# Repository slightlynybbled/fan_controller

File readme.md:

# Purpose #

This repository is for the hardware and firmware for a PC fan controller.  The
controller is intended to allow the user to multi-plex a single motherboard
output so that it may control up to 4 additional fans.  The project will feature:

 * Up to 4 outputs
 * Motherboard-controlled outputs for each with user speed scaling
 * Soft-start to reduce load on the motherboard
 * Speed control for each fan when a motherboard speed signal is not present
 
Details of the project may be found at [for(embed)](http://www.forembed.com/category/fan-controller.html).
 
# Project Status #

Firmware for v1.2 (optional thermistor control) is under development.

Firmware for v1.1 is complete!  Testing has been completely successful!

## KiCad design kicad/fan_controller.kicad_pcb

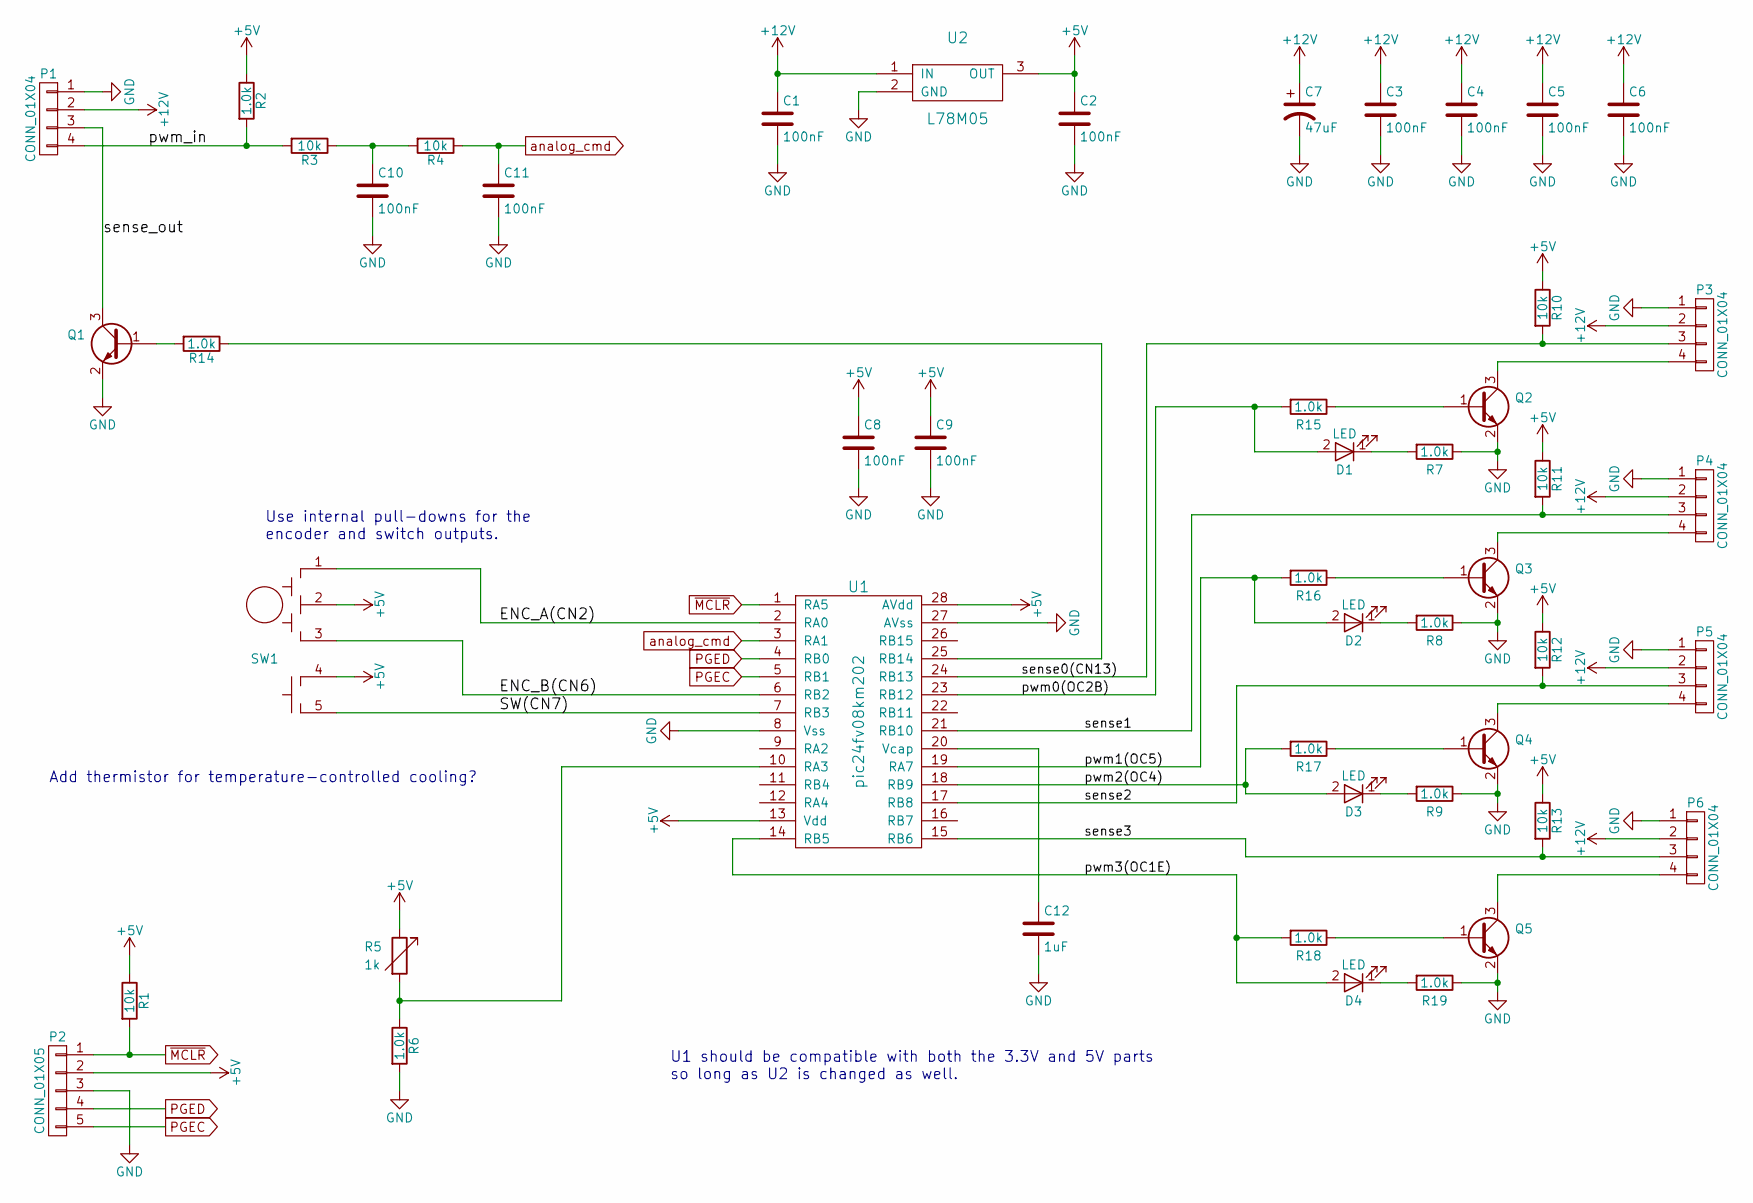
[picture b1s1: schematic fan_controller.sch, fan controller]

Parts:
C1, C2, C3, C4, C5, C6, C8, C9, C10, C11: 100nF; SM_0603; MPN CC0603ZRY5V7BB104
C7: 47uF; C_Radial_D5_L11_P2; MPN ESK476M035AC3AA
C12: 1uF; SM_0603; MPN CC0603ZRY5V7BB105
D1, D2, D3, D4: LED; D_0805; MPN LG R971-KN-1
P1, P3, P4, P5, P6: CONN_01X04; CONN_1x4_PC_FAN; MPN 47053-1000
P2: CONN_01X05; CON_1x5_0.1in
Q1, Q2, Q3, Q4, Q5: Q_NPN_BEC; SOT-23; MPN MMBT3904LT1G
R1, R3, R4, R10, R11, R12, R13: 10k; R_0603; MPN RC0603JR-0710KL
R2, R6, R7, R8, R9, R14, R15, R16, R17, R18, R19: 1.0k; R_0603; MPN RC0603JR-071KL
R5: 1k; D_0805; MPN NCP18XQ102J03RB
SW1: encoder_rotary_with_switch; encoder_EN12-HS; MPN EN12-HS22AF30
U1: pic24fv08km202; SSOP-28; MPN PIC24FV16KM202-I/SS
U2: L78M05; DPAK_TO-252; MPN MC7805CDTG

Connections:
+5V: C2.1, C8.1, C9.1, P2.2, R1.1, R2.1, R5.1, R10.1, R11.1, R12.1, R13.1, SW1.2, SW1.4, U1.13 (Vdd), U1.28 (AVdd), U2.3 (OUT)
+12V: C1.1, C3.1, C4.1, C5.1, C6.1, C7.1, P1.2, P3.2, P4.2, P5.2, P6.2, U2.1 (IN)
/ENC_A(CN2): SW1.1, U1.2 (RA0)
/ENC_B(CN6): SW1.3, U1.6 (RB2)
/SW(CN7): SW1.5, U1.7 (RB3)
/pwm0(OC2B): D1.2 (A), R15.2, U1.23 (RB12)
/pwm1(OC5): D2.2 (A), R16.2, U1.19 (RA7)
/pwm2(OC4): D3.2 (A), R17.2, U1.18 (RB9)
/pwm3(OC1E): D4.2 (A), R18.2, U1.14 (RB5)
/pwm_in: P1.4, R2.2, R3.2
/sense0(CN13): P3.3, R10.2, U1.24 (RB13)
/sense1: P4.3, R11.2, U1.21 (RB10)
/sense2: P5.3, R12.2, U1.17 (RB8)
/sense3: P6.3, R13.2, U1.15 (RB6)
/sense_out: P1.3, Q1.3 (C)
GND: C1.2, C2.2, C3.2, C4.2, C5.2, C6.2, C7.2, C8.2, C9.2, C10.2, C11.2, C12.2, P1.1, P2.3, P3.1, P4.1, P5.1, P6.1, Q1.2 (E), Q2.2 (E), Q3.2 (E), Q4.2 (E), Q5.2 (E), R6.2, R7.1, R8.1, R9.1, R19.1, U1.8 (Vss), U1.27 (AVss), U2.2 (GND)
unnamed: C10.1, R3.1, R4.2
unnamed: C12.1, U1.20 (Vcap)
unnamed: D1.1 (K), R7.2
unnamed: D2.1 (K), R8.2
unnamed: D3.1 (K), R9.2
unnamed: D4.1 (K), R19.2
unnamed: P3.4, Q2.3 (C)
unnamed: P4.4, Q3.3 (C)
unnamed: P5.4, Q4.3 (C)
unnamed: P6.4, Q5.3 (C)
unnamed: Q1.1 (B), R14.2
unnamed: Q2.1 (B), R15.1
unnamed: Q3.1 (B), R16.1
unnamed: Q4.1 (B), R17.1
unnamed: Q5.1 (B), R18.1
unnamed: R5.2, R6.1, U1.10 (RA3)
unnamed: R14.1, U1.25 (RB14)
PGEC: P2.5, U1.5 (RB1)
PGED: P2.4, U1.4 (RB0)
analog_cmd: C11.1, R4.1, U1.3 (RA1)
~MCLR: P2.1, R1.2, U1.1 (RA5)

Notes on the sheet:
U1 should be compatible with both the 3.3V and 5V parts so long as U2 is changed as well.
Add thermistor for temperature-controlled cooling?
Use internal pull-downs for the encoder and switch outputs.

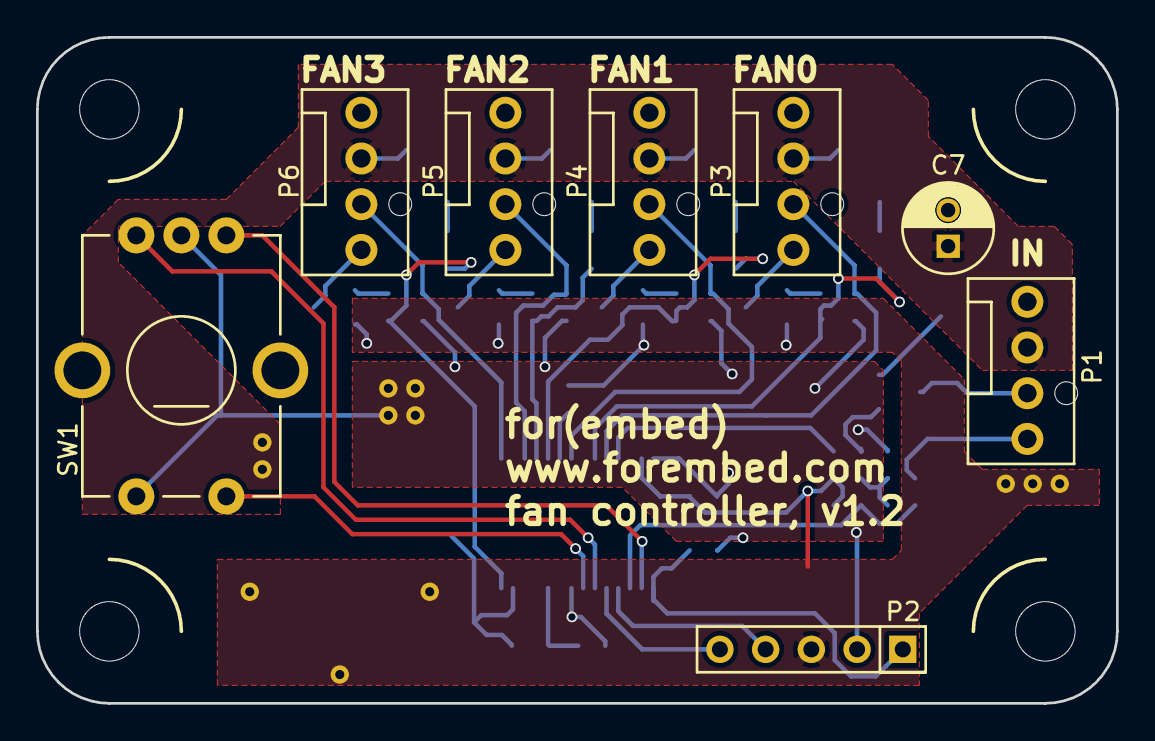
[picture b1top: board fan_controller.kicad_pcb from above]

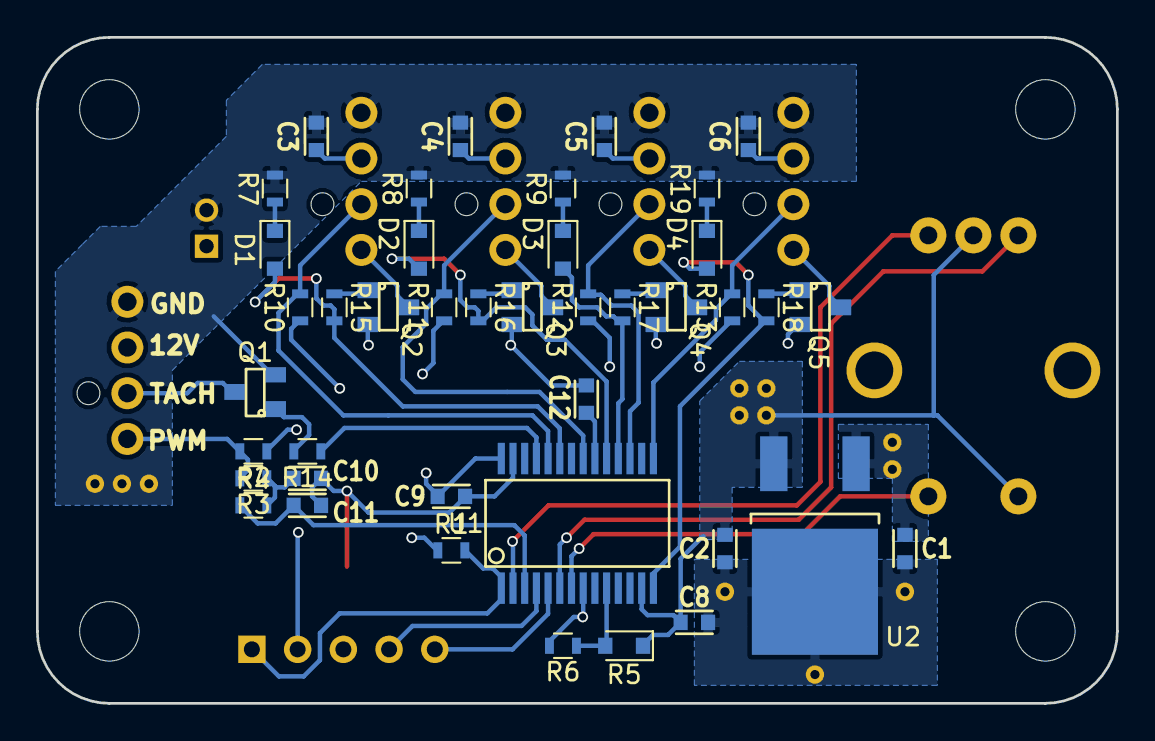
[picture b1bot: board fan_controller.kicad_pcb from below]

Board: 2 copper layers, 60.0 x 37.0 mm, 49 parts (41 on the bottom side), 37 nets.

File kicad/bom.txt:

Item	Qty	Reference	Manufacturer	MPN	Description	Datasheet
1	10	 C1, C2, C3, C4, C5, C6, C8, C9, C10, C11	Yageo	CC0603ZRY5V7BB104	capacitor, 100nF, 0603	
2	1	 C12	Yageo	CC0603ZRY5V7BB105	capacitor, ceramic, 1uF 16V	
3	1	 C7	Kemet	ESK476M035AC3AA	capacitor, alum, 47uF 35V, radial	
4	4	 D1, D2, D3, D4	OSRAM Opto Semiconductors Inc.	LG R971-KN-1	LED, green	
5	5	 P1, P3, P4, P5, P6	Molex	47053-1000	PC fan connector, 4-pin	
6	1	 P2				
7	5	 Q1, Q2, Q3, Q4, Q5	ON Semiconductor	MMBT3904LT1G	transistor, npn, 40V 0.2A SOT-23	
8	7	 R1, R3, R4, R10, R11, R12, R13	Yageo	RC0603JR-0710KL	resistor, 10k, 0603	
9	11	 R2, R6, R7, R8, R9, R14, R15, R16, R17, R18, R19	Yageo	RC0603JR-071KL	resistor, 1k, 0603	
10	1	 R5	Murata Electronics North America	NCP18XQ102J03RB	Thermistor, NTC	
11	1	 SW1	TT Electronics/BI	EN12-HS22AF30	encoder, rotary, top-adjust with switch	
12	1	 U1	Microchip, Inc.	PIC24FV16KM202-I/SS	microcontroller, 5V, 16MIPS	
13	1	 U2	ON Semiconductor	MC7805CDTG	voltage regulator, linear, 5V 1A, DPAK

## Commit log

2016-07-11 Initial design
2016-07-11 Added PDF schematic for easy review
2016-07-11 Added readme
2016-07-11 Added website pointer
2016-07-17 Project builds, un-tested
2016-07-18 Oscillator and task manager along with some PWMs working
2016-07-18 Added gitignore file
2016-07-18 Added MIT license
2016-07-18 All PWMs work
2016-07-18 Inverted the output PWMs
2016-07-18 CN interrupts working
2016-07-18 Encoder being polled by the task manager
2016-07-18 Fixed bug in code
2016-07-18 Reading and debouncing the switch
2016-07-18 Added state machine to fan controller that has a timeout
2016-07-18 Removed debugging pin toggle
2016-07-19 State machine is working
2016-07-19 Added target duty cycle setter at the end of adjustment
2016-07-19 Have basic EEPROM working
2016-07-19 Saving values to EEPROM
2016-07-19 Removed commented code
2016-07-19 CN inputs and scaling added
2016-07-19 Tach output works
2016-07-19 Added spacing for clarity
2016-07-20 Renamed function
2016-07-20 Accounting for stored '0xffff' values in EEPROM on initialization
2016-07-20 Fixed index error
2016-07-20 Fixed an error in which the address wasn't even as the device requires
2016-07-20 Fixed the initializer check for the EEPROM
2016-07-20 Fixed state machine and PWM on 'normal' state
2016-07-20 Removed pulse time measurement in CN
2016-07-21 Activated CN pull-down resistors within the uC
2016-07-21 Added hardware files for v1.1 schematic and board
2016-07-21 PDF print
2016-08-05 Added missing BOM information
2016-08-05 Updated pin functionality for v1.1 of the board
2016-08-16 Added ADC conversion to measure input PWM
2016-08-16 Converted to 'safer' subtract
2016-08-16 Added net label
2017-06-08 Added LEDs, fixed #2
2017-06-08 Added logo
2017-06-08 Updating to v1.2 (adding thermistor and LED)
2017-06-08 Corrected silkscreen, added images to readme
